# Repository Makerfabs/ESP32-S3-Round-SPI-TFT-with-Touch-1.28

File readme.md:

# ESP32-S3 Round SPI TFT with Touch 1.28"

```c++
/*
Version:        V1.1
Author:            Vincent
Create Date:    2023/2/18
Note:
        2023/4/15 V1.1:Add TFT_eSPI support.
*/
```

[TOC]

# Makerfabs

[Makerfabs home page](https://www.makerfabs.com/)

[Makerfabs Wiki](https://wiki.makerfabs.com/)

# ESP32-S3 Round SPI TFT with Touch 1.28"

## Intruduce

Product Link ：[ESP32-S3 Round SPI TFT with Touch 1.28"](https://www.makerfabs.com/esp32-s3-round-spi-tft-with-touch-1-28-inch.html)

Wiki Link : 

The ESP32-S3 round display with touch can be a great tool for your applications such as smartwatch.

We selected the ESP32-S3 generation as the controller, with 16MB Flash and 8MB PSRAM, enough for most IOT applications; The round display is 240x240 resolution 1.28", colorful RGB, with capacitive touch, it communicates with ESP32 with SPI interface, so there enough GPIO left for expansion applications.

## Feature

- Controller: ESP32-S3
- Wireless: WiFi& Bluetooth 5.0
- LCD: 1.28", 240*240 resolution, driver GC9A01
- LCD interface: SPI
- Touch Panel Driver: CST816S
- USB: USB Native
- Power Supply: USB Type-C 5.0V(4.0V~5.25V); 3.7V Lipo battery
- Button: Flash button and reset button
- Mabee interface: 1*I2C; 1*GPIO
- MicroSD: Yes
- Arduino support: Yes
- Operation temperature: -40℃ to +85℃

# Code

## Complier Option

- Install board : ESP32 .
- Install libraries：

- Use type-c use cable connect USB to PC.
- Select "ESP32-S3 DEV Module"

"mf_Lvgl" library is modified from Lvgl library (version 8.3.2). 

If you want use lvgl, please unzip "lib/mf_Lvgl.zip" and copy to arduino library directory.

## Factory test program

\example\esp32s3_round_test

You can run this file test if you feel that your hardware is not working properly. 

Need copy logo_240240.jpg to sd card.

## Example

### TFT_eSPI demo

Add TFT_eSPI support.

Library version is 2.5.0

And cover "User_Setuo.h" to library directry.

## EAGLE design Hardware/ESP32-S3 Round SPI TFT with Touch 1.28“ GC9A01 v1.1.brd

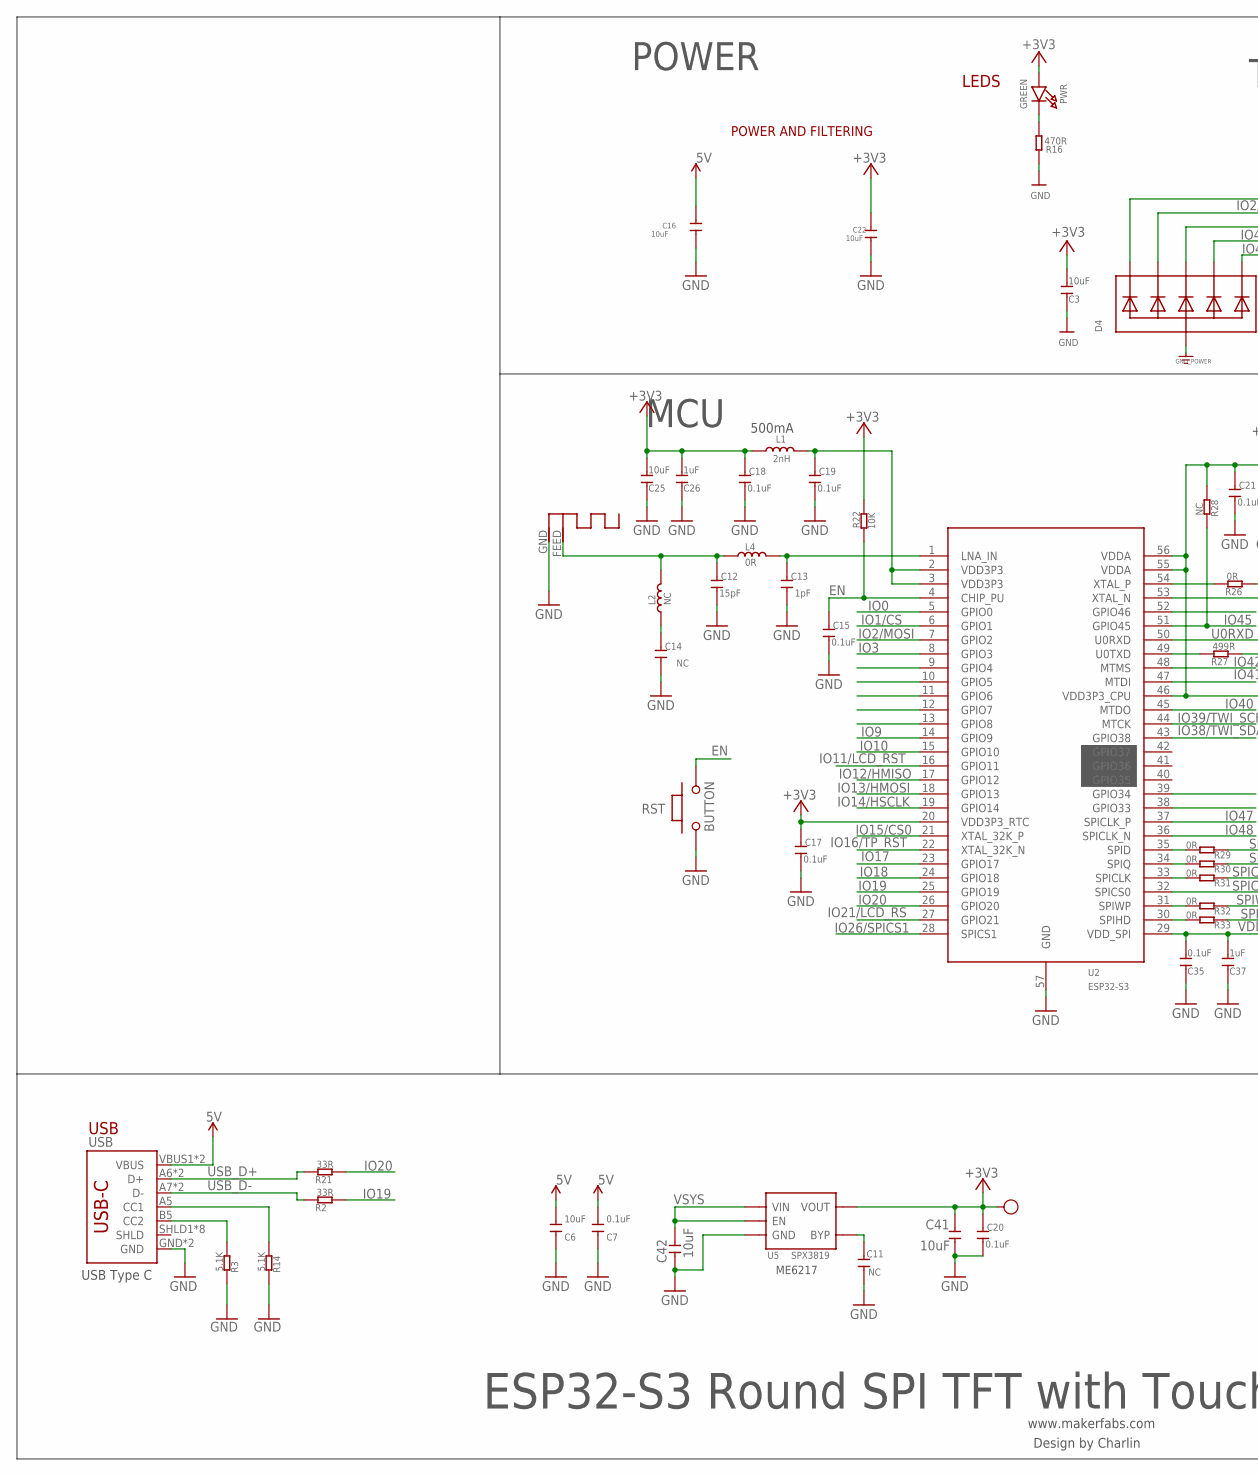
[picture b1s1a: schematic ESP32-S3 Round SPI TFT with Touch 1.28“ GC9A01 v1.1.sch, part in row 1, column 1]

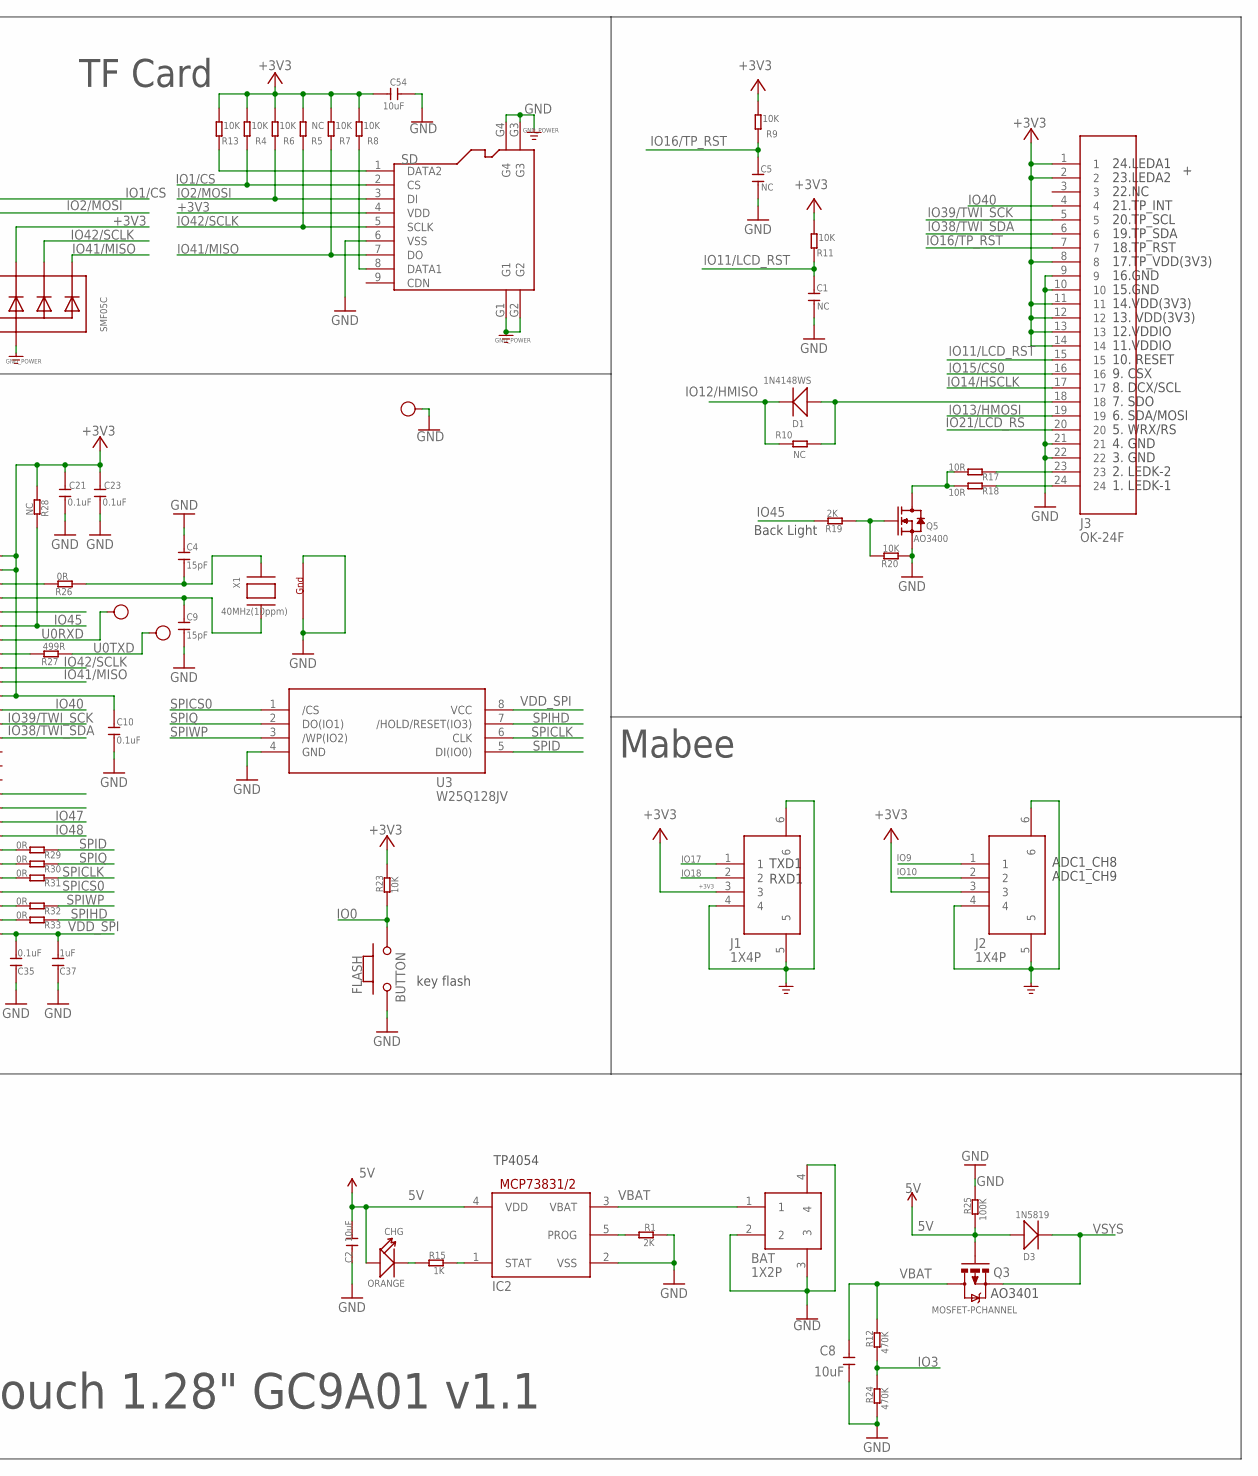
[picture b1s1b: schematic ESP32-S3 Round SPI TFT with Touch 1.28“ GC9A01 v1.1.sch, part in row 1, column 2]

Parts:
3V3: TEST-POINT'4545'; TP-D45MIL; PARTNO DNP
ANT1: ANTENNA; RN-ANT
BAT: 1X2P; 1X2P-SMT1.25MM
C1, C5, C11, C14: NC; DISCRETE_C0402
C2, C8, C16, C22, C41, C42: 10uF; C0603
C3, C6, C25, C54: 10uF; DISCRETE_C0603
C4, C9, C12: 15pF; DISCRETE_C0402
C7, C35: 0.1uF; DISCRETE_C0603
C10, C15, C17, C18, C19, C20, C21, C23: 0.1uF; DISCRETE_C0402
C13: 1pF; DISCRETE_C0402
C26, C37: 1uF; DISCRETE_C0603
CHG: ORANGE; D0603
D1: 1N4148WS; SOD323
D3: 1N5819; SOD323
D4: SMF05C; SOT363
FLASH: BUTTON; 157SW
GND: TEST-POINT'4545'; TP-D45MIL
IC2: MCP73831/OT; SOT23-5L
J1, J2: 1X4P; 1X4P-SMT1.25MM
J3: OK-24F; OK-24F-0.4
L1: 2nH; DISCRETE_L0603
L2: NC; DISCRETE_L0402
L4: 0R; DISCRETE_L0402
PWR: GREEN; CHIPLED_0805_NOOUTLINE
Q3: MOSFET-PCHANNEL; SOT23-3
Q5: AO3400; SOT23@1
R1, R19: 2K; DISCRETE_R0402
R2, R21: 33R; DISCRETE_R0402
R3, R14: 5.1K; DISCRETE_R0402
R4, R6, R7, R8, R9, R11, R13, R20, R22, R23: 10K; DISCRETE_R0402
R5, R28: NC; DISCRETE_R0402
R10: NC; R0603
R12, R24: 470K; DISCRETE_R0402
R15: 1K; DISCRETE_R0402
R16: 470R; DISCRETE_R0402
R17, R18: 10R; DISCRETE_R0402
R25: 100K; DISCRETE_R0402
R26, R29, R30, R31, R32, R33: 0R; DISCRETE_R0402
R27: 499R; DISCRETE_R0402
RST: BUTTON; 157SW
RX: TEST-POINT'4545'; TP-D45MIL; PARTNO DNP
SD: HOLDER-MICROSD-9P; 9P-SMD-W/-RING
TX: TEST-POINT'4545'; TP-D45MIL; PARTNO DNP
U2: ESP32-S3; QFN56-7*7MM
U3: W25Q128JV; SOIC-8-208MIL
U5: SPX3819; SOT23-5
USB: USB_C5; USB-C-16P-5
X1: 40MHz(10ppm); NX3225

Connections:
5V: C2.2, C6.2, C7.2, C16.1, CHG.+, D3.+, IC2.4 (VDD), Q3.1 (G), R25.1, USB.VBUS1 (VBUS), USB.VBUS2 (VBUS)
+3V3: 3V3.T, C3.2, C10.2, C17.2, C18.2, C20.2, C21.2, C22.1, C23.2, C25.2, C26.2, C41.2, C54.2, D4.4 (C3), J1.3, J2.3, J3.1, J3.2, J3.8, J3.11, J3.12, J3.13, J3.14, L1.1, PWR.A, R4.2, R5.2, R6.2, R7.2, R8.2, R9.2, R11.2, R13.2, R22.2, R23.2, R28.1, SD.4 (VDD), U2.20 (VDD3P3_RTC), U2.46 (VDD3P3_CPU), U2.55 (VDDA), U2.56 (VDDA), U5.5 (VOUT)
EN: C15.2, R22.1, RST.2, U2.4 (CHIP_PU)
GND: ANT1.GND, BAT.2, BAT.3, BAT.4, C1.1, C2.1, C3.1, C4.2, C5.1, C6.1, C7.1, C8.1, C9.1, C10.1, C11.1, C12.1, C13.1, C14.1, C15.1, C16.2, C17.1, C18.1, C19.1, C20.1, C21.1, C22.2, C23.1, C25.1, C26.1, C35.1, C37.1, C41.1, C42.1, C54.1, D4.2 (A), FLASH.1, GND.T, IC2.2 (VSS), J1.4, J1.5, J1.6, J2.4, J2.5, J2.6, J3.9, J3.10, J3.21, J3.22, Q5.2 (S), R1.2, R3.2, R14.2, R16.1, R20.1, R24.1, R25.2, RST.1, SD.6 (VSS), SD.G1, SD.G2, SD.G3, SD.G4, U2.57 (GND), U3.4 (GND), U5.2 (GND), USB.GND, USB.GND2 (GND), X1.2 (G2), X1.4 (G1)
IO0: FLASH.2, R23.1, U2.5 (GPIO0)
IO1/CS: D4.1 (C1), R4.1, SD.2 (CS), U2.6 (GPIO1)
IO2/MOSI: D4.3 (C2), R6.1, SD.3 (DI), U2.7 (GPIO2)
IO3: R12.1, R24.2, U2.8 (GPIO3)
IO9: J2.1, U2.14 (GPIO9)
IO10: J2.2, U2.15 (GPIO10)
IO11/LCD_RST: C1.2, J3.15, R11.1, U2.16 (GPIO11)
IO12/HMISO: D1.-, R10.1, U2.17 (GPIO12)
IO13/HMOSI: J3.19, U2.18 (GPIO13)
IO14/HSCLK: J3.17, U2.19 (GPIO14)
IO15/CS0: J3.16, U2.21 (XTAL_32K_P)
IO16/TP_RST: C5.2, J3.7, R9.1, U2.22 (XTAL_32K_N)
IO17: J1.1, U2.23 (GPIO17)
IO18: J1.2, U2.24 (GPIO18)
IO19: R2.1, U2.25 (GPIO19)
IO20: R21.1, U2.26 (GPIO20)
IO21/LCD_RS: J3.20, U2.27 (GPIO21)
IO26/SPICS1: U2.28 (SPICS1)
IO38/TWI_SDA: J3.6, U2.43 (GPIO38)
IO39/TWI_SCK: J3.5, U2.44 (MTCK)
IO40: J3.4, U2.45 (MTDO)
IO41/MISO: D4.6 (C5), R7.1, SD.7 (DO), U2.47 (MTDI)
IO42/SCLK: D4.5 (C4), R5.1, SD.5 (SCLK), U2.48 (MTMS)
IO45: R19.2, R28.2, U2.51 (GPIO45)
IO47: U2.37 (SPICLK_P)
IO48: U2.36 (SPICLK_N)
unnamed: D1.+, J3.18, R10.2
unnamed: IC2.5 (PROG), R1.1
unnamed: R14.1, USB.A5 (CC1)
unnamed: PWR.C, R16.2
unnamed: R3.1, USB.B5 (CC2)
unnamed: Q5.1 (G), R19.1, R20.2
unnamed: J3.23, R17.1
unnamed: Q5.3 (D), R17.2, R18.2
unnamed: CHG.-, R15.1
unnamed: IC2.1 (STAT), R15.2
unnamed: ANT1.FEED, C12.2, L2.2, L4.1
unnamed: C13.2, L4.2, U2.1 (LNA_IN)
unnamed: R29.2, U2.35 (SPID)
unnamed: C19.2, L1.2, U2.2 (VDD3P3), U2.3 (VDD3P3)
unnamed: C14.2, L2.1
unnamed: R30.2, U2.34 (SPIQ)
unnamed: R26.2, U2.54 (XTAL_P)
unnamed: R31.2, U2.33 (SPICLK)
unnamed: R32.2, U2.31 (SPIWP)
unnamed: R33.2, U2.30 (SPIHD)
unnamed: R13.1, SD.1 (DATA2)
unnamed: R8.1, SD.8 (DATA1)
unnamed: R27.2, U2.49 (U0TXD)
unnamed: C9.2, U2.53 (XTAL_N), X1.3 (X2)
unnamed: C4.1, R26.1, X1.1 (X1)
unnamed: J3.24, R18.1
unnamed: C11.2, U5.4 (BYP)
SPICLK: R31.1, U3.6 (CLK)
SPICS0: U2.32 (SPICS0), U3.1 (/CS)
SPID: R29.1, U3.5 (DI(IO0))
SPIHD: R33.1, U3.7 (/HOLD/RESET(IO3))
SPIQ: R30.1, U3.2 (DO(IO1))
SPIWP: R32.1, U3.3 (/WP(IO2))
U0RXD: RX.T, U2.50 (U0RXD)
U0TXD: R27.1, TX.T
USB_D+: R21.2, USB.A6 (D+), USB.B6 (D+)
USB_D-: R2.2, USB.A7 (D-), USB.B7 (D-)
VBAT: BAT.1, C8.2, IC2.3 (VBAT), Q3.3 (D), R12.2
VDD_SPI: C35.2, C37.2, U2.29 (VDD_SPI), U3.8 (VCC)
VSYS: C42.2, D3.-, Q3.2 (S), U5.1 (VIN), U5.3 (EN)

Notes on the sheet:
www.makerfabs.com
Design by Charlin
LEDS
POWER AND FILTERING
key flash
ESP32-S3 Round SPI TFT with Touch 1.28" GC9A01 v1.1
POWER
TF Card
USB
USB Type C
Mabee
MCU
500mA
ME6217
1. LEDK-1
2. LEDK-2
3. GND
4. GND
5. WRX/RS
6. SDA/MOSI
7. SDO
8. DCX/SCL
9. CSX
10. RESET
11.VDDIO
12.VDDIO
13. VDD(3V3)
14.VDD(3V3)
15.GND
16.GND
17.TP_VDD(3V3)
18.TP_RST
19.TP_SDA
20.TP_SCL
21.TP_INT
22.NC
23.LEDA2
24.LEDA1
Back Light
ADC1_CH8

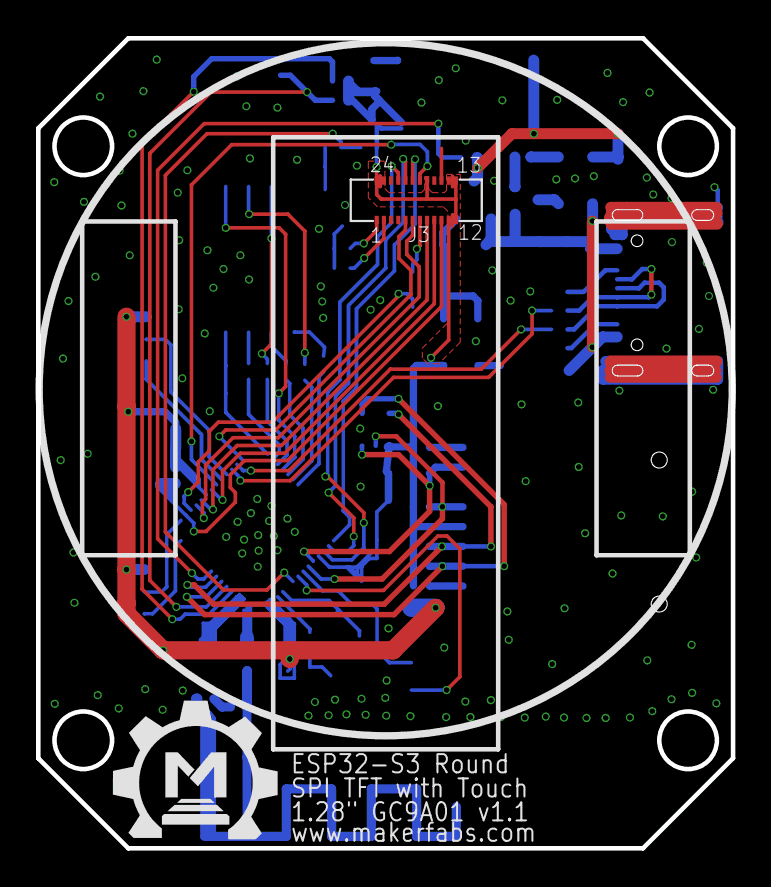
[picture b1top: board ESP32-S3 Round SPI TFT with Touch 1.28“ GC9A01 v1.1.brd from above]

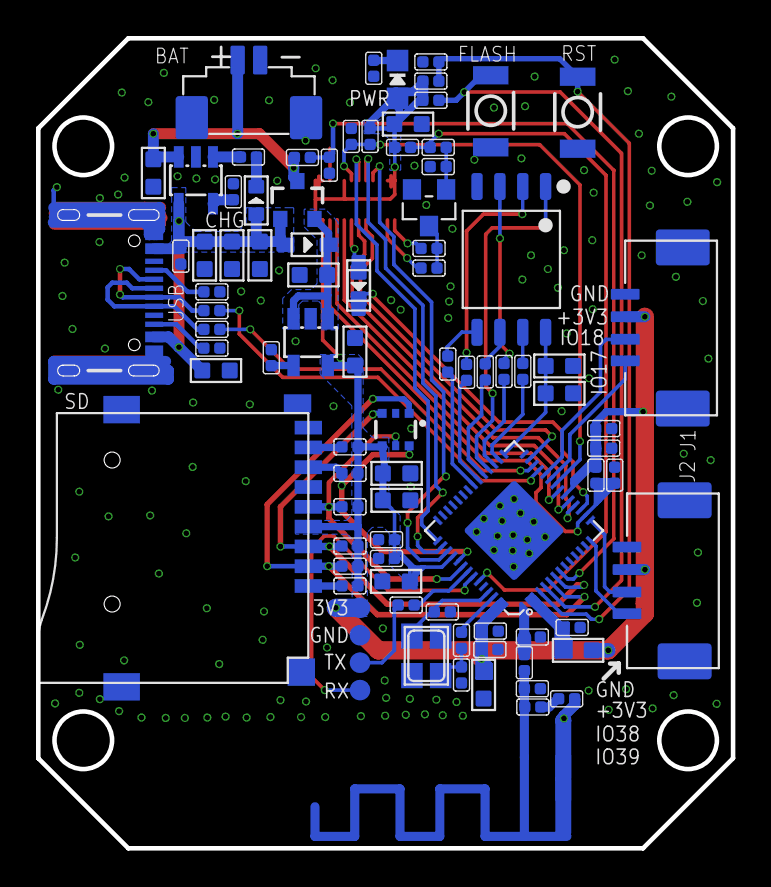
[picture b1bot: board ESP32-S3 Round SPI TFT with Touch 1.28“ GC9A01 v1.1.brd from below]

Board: 2 copper layers, 38.6 x 45.0 mm, 92 parts (90 on the bottom side), 67 nets.

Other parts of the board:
U$1: MAKERFABS_0.3

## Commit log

2023-02-07 Create project
2023-02-08 Out factory code
2023-02-13 Add example
2023-02-14 Add gif display
2023-02-14 LVGL demo
2023-02-14 Add auto point mode
2023-02-15 Display 5 gif
2023-02-18 Edit readme
2023-03-16 add hardware
2023-04-15 V1.1 TFT_eSPI support
2023-05-19 Add spiffs demo
2023-10-28 Add LVGL ADC example

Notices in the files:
parts and their libraries:
microbuilder: This work is placed in the public domain, and may be freely used for commercial and non-commercial work with the following conditions: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
User-Submitted: Licensing: Creative Commons ShareAlike 4.0 International - https://creativecommons.org/licenses/by-sa/4.0
